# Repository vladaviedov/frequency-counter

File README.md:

# Frequency Counter

Design files & firmware for my [frequency counter
project](https://vladaviedov.org/project/frequency_counter.html)

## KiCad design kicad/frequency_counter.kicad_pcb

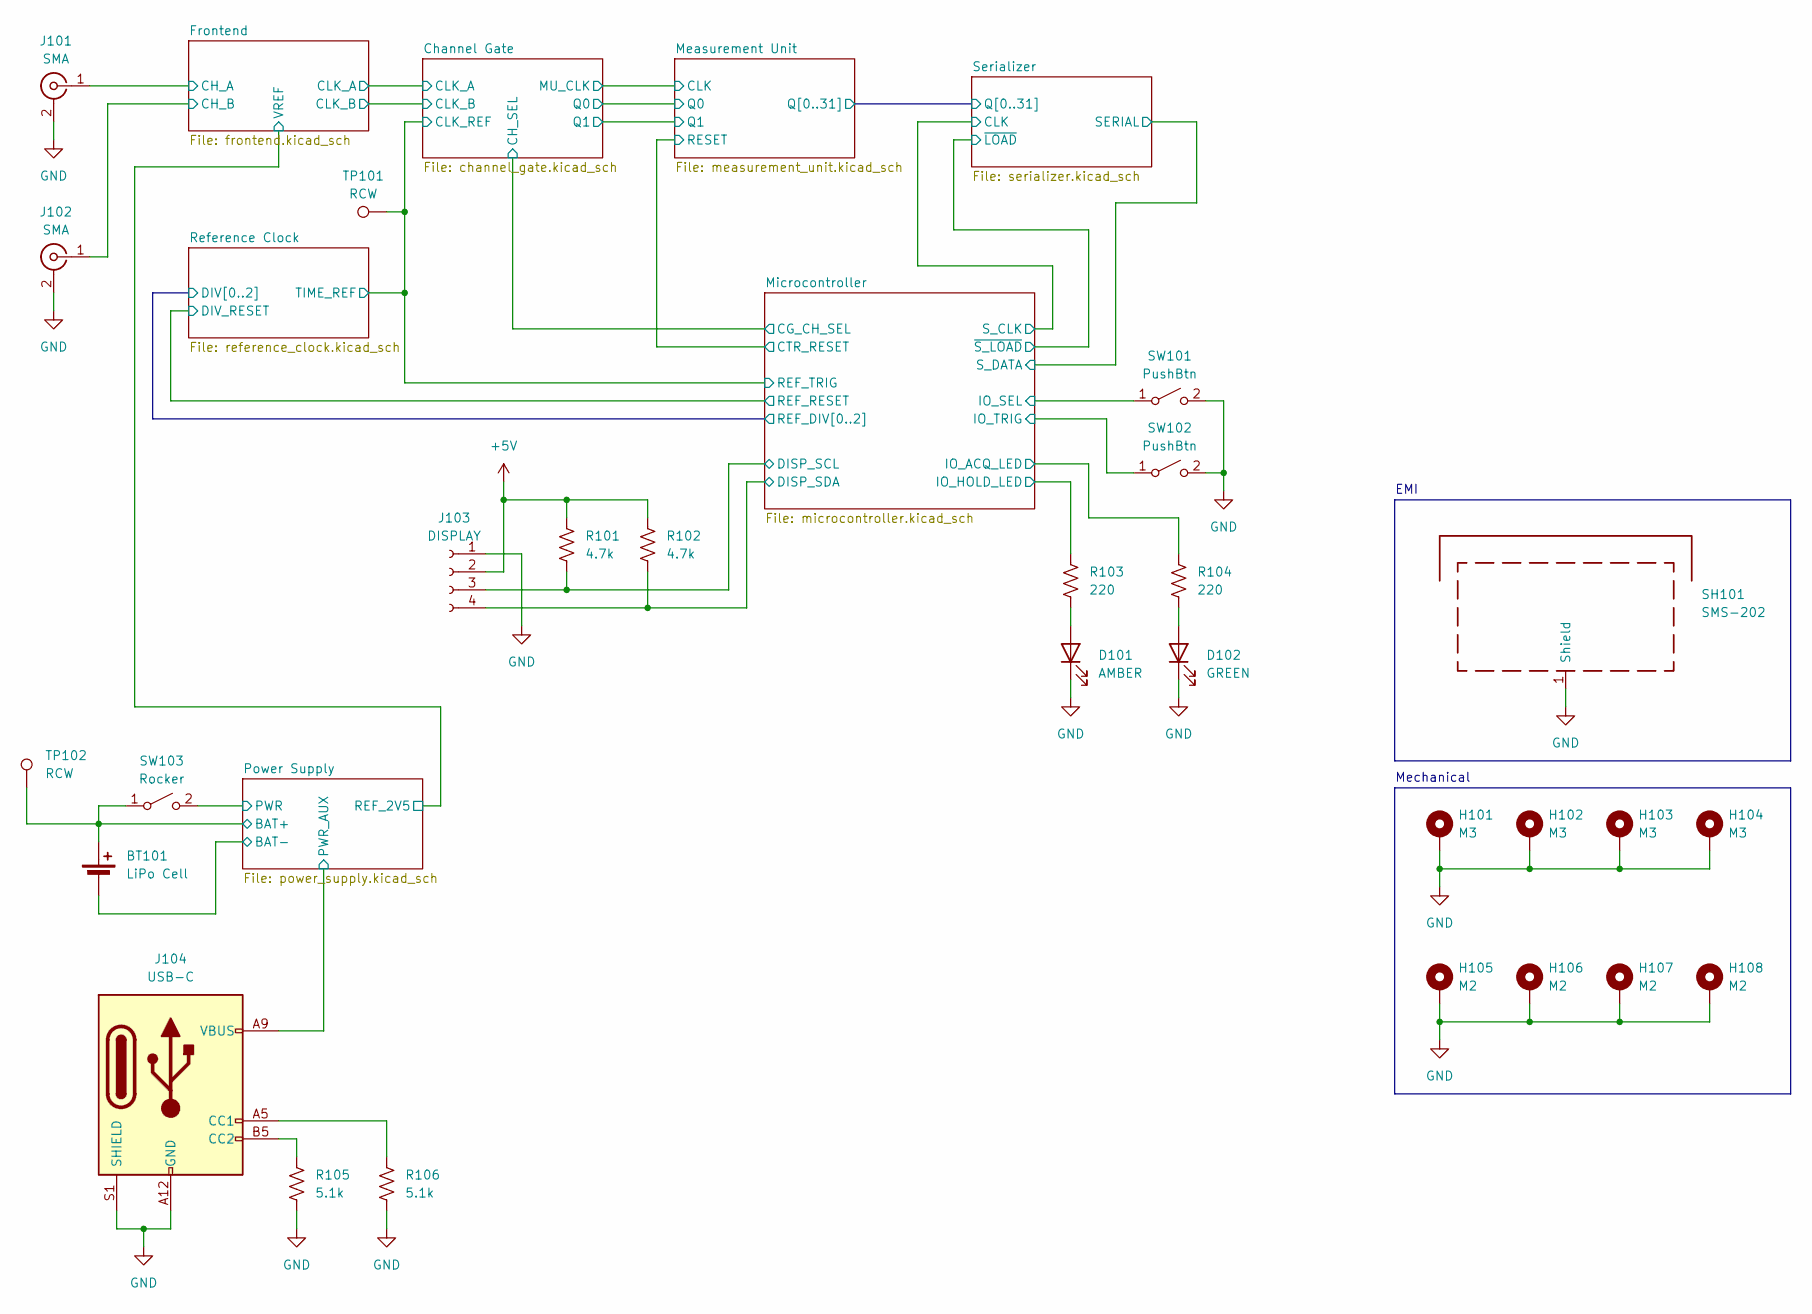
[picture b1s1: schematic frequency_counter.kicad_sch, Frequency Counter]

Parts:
BT101: LiPo Cell; JST_ZH_B2B-ZR_1x02_P1.50mm_Vertical
D101: AMBER; LED_0603_1608Metric; MPN B1911UY--20D000114U1930
D102: GREEN; LED_0603_1608Metric; MPN B1911NG--20D000214U1930
H101, H102, H103, H104: M3; MountingHole_3.2mm_M3_Pad
H105, H106, H107, H108: M2; MountingHole_2.2mm_M2_Pad
J101, J102: SMA; SMA_Adjusted; MPN CON-SMA-EDGE-S
J103: DISPLAY; PinHeader_1x04_P2.54mm_Vertical
J104: USB-C; USB_C_Receptacle_GCT_USB4125-xx-x_6P_TopMnt_Horizontal; MPN USB4125-GF-A
R101, R102: 4.7k; R_0402_1005Metric_Fix; MPN RC0402JR-074K7L
R103, R104: 220; R_0402_1005Metric_Fix; MPN RC0402JR-13220RL
R105, R106: 5.1k; R_0402_1005Metric_Fix; MPN RC0402JR-135K1L
SH101: SMS-202; Laird_Technologies_BMI-S-202-F_16.50x16.50mm; MPN SMS-201F
SW101, SW102: PushBtn; SW_Push_1P1T_NO_E-Switch_TL3301NxxxxxG; MPN 2-1977223-4
SW103: Rocker; SolderWire-1.5sqmm_1x02_P6mm_D1.7mm_OD3mm
TP101, TP102: RCW; TestPoint_KOA_RCW; MPN RCWCTE

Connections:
+5V: J103.2, R101.1, R102.1; also elsewhere on the board
/Channel Gate/CLK_REF: TP101.1; also elsewhere on the board
/Frontend/CH_A: J101.1 (In); also elsewhere on the board
/Frontend/CH_B: J102.1 (In); also elsewhere on the board
/Microcontroller/DISP_SCL: J103.3, R101.2; also elsewhere on the board
/Microcontroller/DISP_SDA: J103.4, R102.2; also elsewhere on the board
/Microcontroller/IO_ACQ_LED: R104.1; also elsewhere on the board
/Microcontroller/IO_HOLD_LED: R103.1; also elsewhere on the board
/Microcontroller/IO_SEL: SW101.1 (A); also elsewhere on the board
/Microcontroller/IO_TRIG: SW102.1 (A); also elsewhere on the board
/Power Supply/BAT+: BT101.1 (+), SW103.1 (A), TP102.1; also elsewhere on the board
/Power Supply/BAT-: BT101.2 (-); also elsewhere on the board
/Power Supply/PWR: SW103.2 (B); also elsewhere on the board
/Power Supply/PWR_AUX: J104.A9 (VBUS), J104.B9 (VBUS); also elsewhere on the board
GND: D101.1 (K), D102.1 (K), H101.1, H102.1, H103.1, H104.1, H105.1, H106.1, H107.1, H108.1, J101.2 (Ext), J102.2 (Ext), J103.1, J104.A12 (GND), J104.B12 (GND), J104.S1 (SHIELD), R105.2, R106.2, SH101.1 (Shield), SW101.2 (B), SW102.2 (B); also elsewhere on the board
unnamed: D101.2 (A), R103.2
unnamed: D102.2 (A), R104.2
unnamed: J104.A5 (CC1), R106.1
unnamed: J104.B5 (CC2), R105.1

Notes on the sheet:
Mechanical
EMI

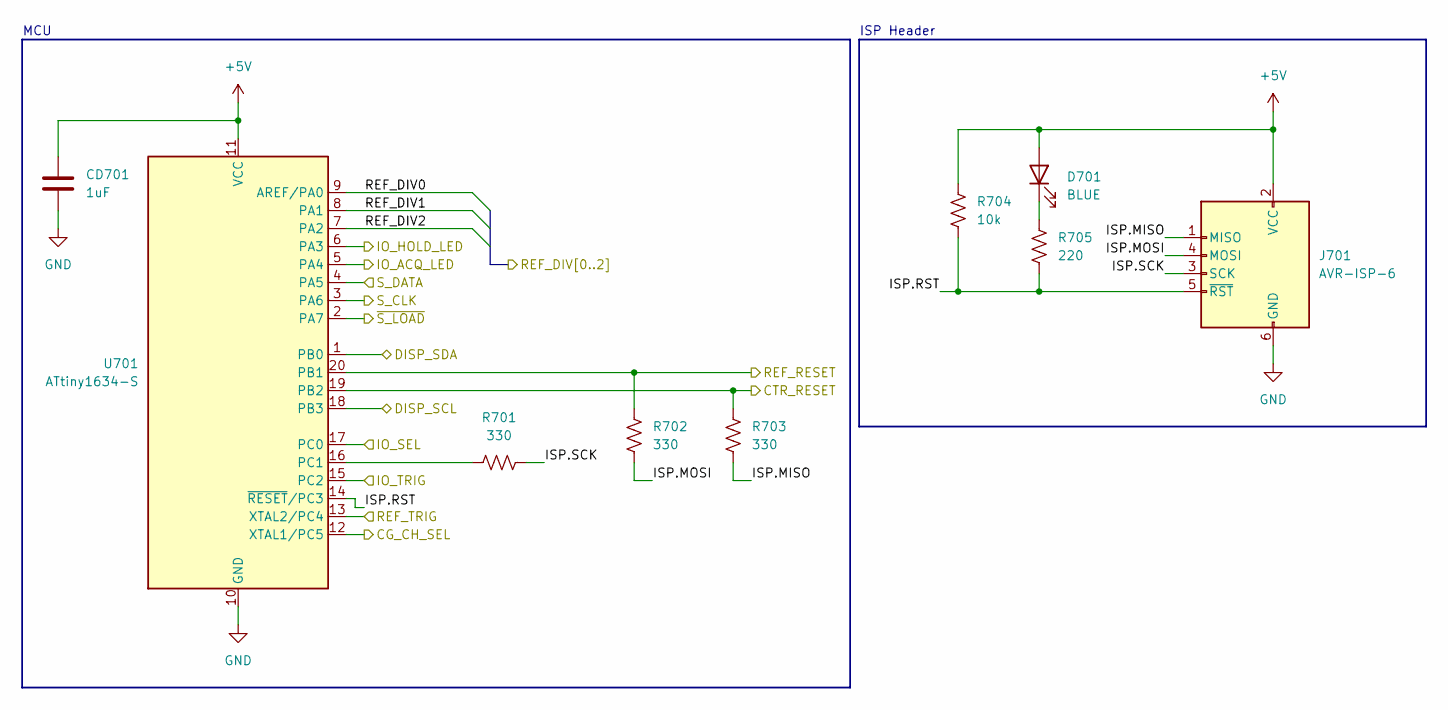
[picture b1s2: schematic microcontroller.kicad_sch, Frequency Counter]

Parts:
CD701: 1uF; C_0402_1005Metric_Fix; MPN 0402ZD105KAT2A
D701: BLUE; LED_0603_1608Metric; MPN E1221NB--05D000814U1930
J701: AVR-ISP-6; IDC-Header_2x03_P2.54mm_Vertical
R701, R702, R703: 330; R_0402_1005Metric_Fix; MPN RC0402JR-13330RL
R704: 10k; R_0402_1005Metric_Fix; MPN RC0402JR-1310KL
R705: 220; R_0402_1005Metric_Fix; MPN RC0402JR-13220RL
U701: ATtiny1634-S; SOIC-20W_7.5x12.8mm_P1.27mm; MPN ATTINY1634-SU

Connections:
+5V: CD701.1, D701.2 (A), J701.2 (VCC), R704.1, U701.11 (VCC); also elsewhere on the board
/Channel Gate/CH_SEL: U701.12 (XTAL1/PC5); also elsewhere on the board
/Channel Gate/CLK_REF: U701.13 (XTAL2/PC4); also elsewhere on the board
/Measurement Unit/RESET: R703.2, U701.19 (PB2); also elsewhere on the board
/Microcontroller/DISP_SCL: U701.18 (PB3); also elsewhere on the board
/Microcontroller/DISP_SDA: U701.1 (PB0); also elsewhere on the board
/Microcontroller/IO_ACQ_LED: U701.5 (PA4); also elsewhere on the board
/Microcontroller/IO_HOLD_LED: U701.6 (PA3); also elsewhere on the board
/Microcontroller/IO_SEL: U701.17 (PC0); also elsewhere on the board
/Microcontroller/IO_TRIG: U701.15 (PC2); also elsewhere on the board
/Microcontroller/ISP.MISO: J701.1 (MISO), R703.1
/Microcontroller/ISP.MOSI: J701.4 (MOSI), R702.2
/Microcontroller/ISP.RST: J701.5 (~RST), R704.2, R705.1, U701.14 (~RESET/PC3)
/Microcontroller/ISP.SCK: J701.3 (SCK), R701.1
/Microcontroller/REF_DIV0: U701.9 (AREF/PA0); also elsewhere on the board
/Microcontroller/REF_DIV1: U701.8 (PA1); also elsewhere on the board
/Microcontroller/REF_DIV2: U701.7 (PA2); also elsewhere on the board
/Microcontroller/REF_RESET: R702.1, U701.20 (PB1); also elsewhere on the board
/Microcontroller/S_CLK: U701.3 (PA6); also elsewhere on the board
/Microcontroller/S_DATA: U701.4 (PA5); also elsewhere on the board
/Microcontroller/~S_LOAD: U701.2 (PA7); also elsewhere on the board
GND: CD701.2, J701.6 (GND), U701.10 (GND); also elsewhere on the board
unnamed: D701.1 (K), R705.2
unnamed: R701.2, U701.16 (PC1)

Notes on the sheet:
MCU
ISP Header

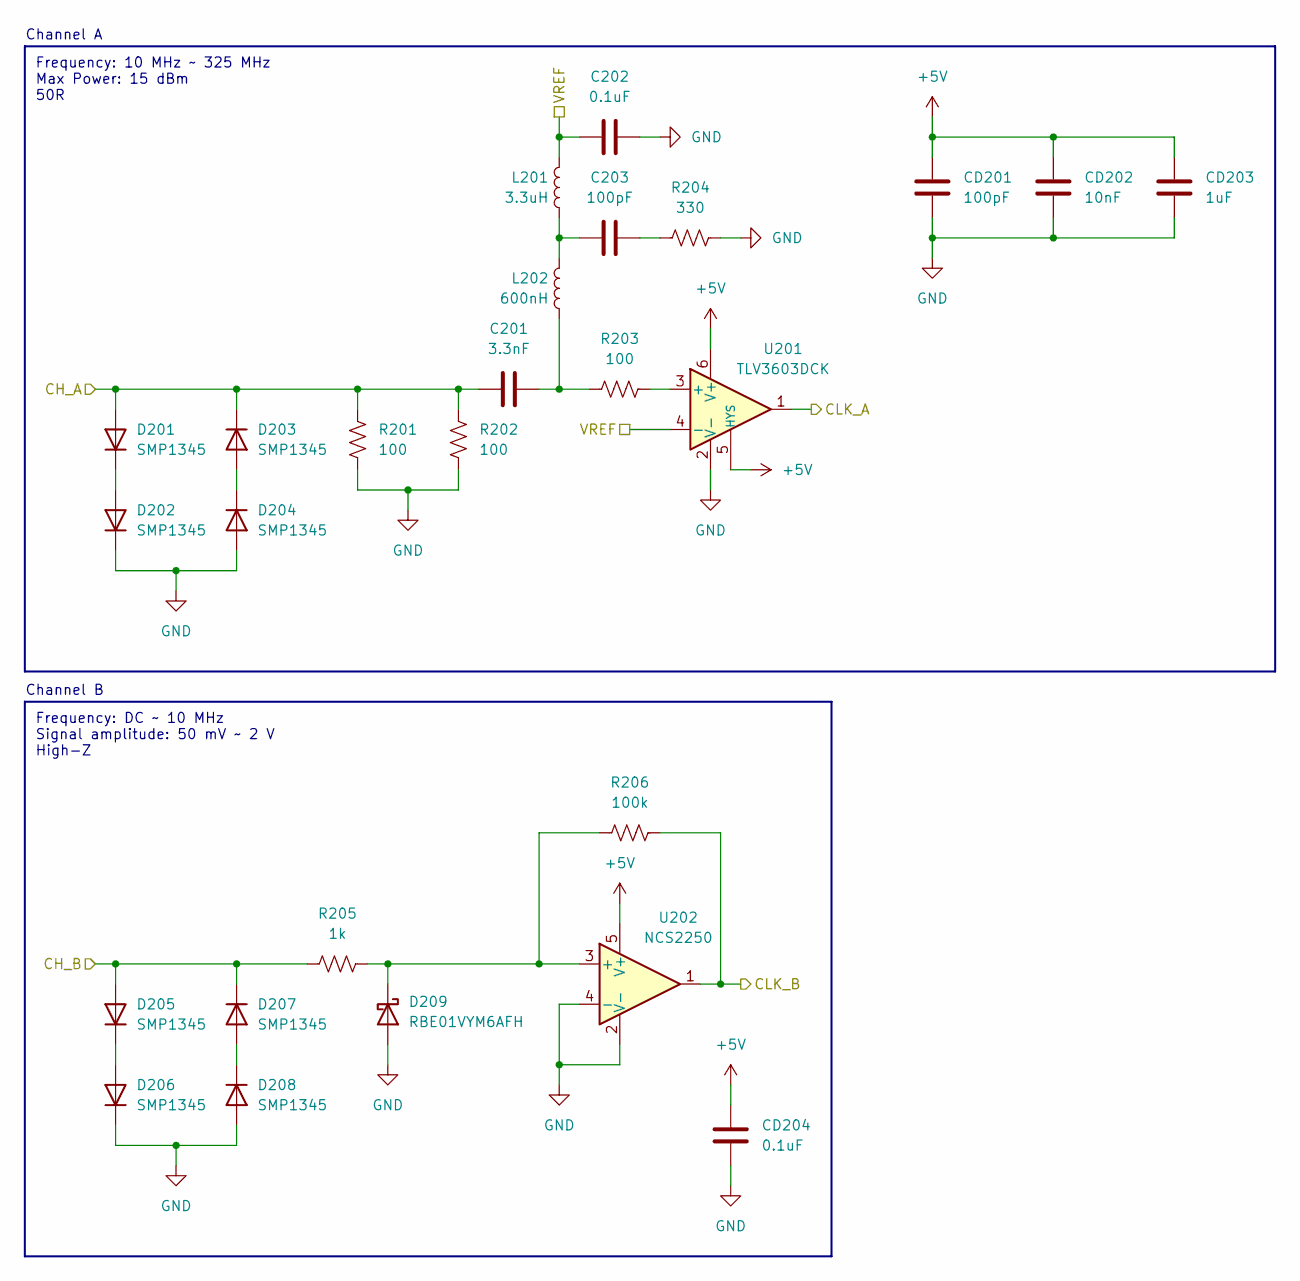
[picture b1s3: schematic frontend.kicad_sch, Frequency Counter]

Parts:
C201: 3.3nF; C_0402_1005Metric_Fix; MPN GRM1555C1H332JE01D
C202: 0.1uF; C_0402_1005Metric_Fix; MPN KGM05AR51C104KH
C203: 100pF; C_0402_1005Metric_Fix; MPN CC0402JRNPO9BN101
CD201: 100pF; C_0402_1005Metric_Fix; MPN CC0402JRNPO9BN101
CD202: 10nF; C_0402_1005Metric_Fix; MPN GRM155R71C103KA01D
CD203: 1uF; C_0402_1005Metric_Fix; MPN 0402ZD105KAT2A
CD204: 0.1uF; C_0402_1005Metric_Fix; MPN KGM05AR51C104KH
D201, D202, D203, D204, D205, D206, D207, D208: SMP1345; D_0402_1005Metric_Pad0.77x0.64mm_HandSolder; MPN SMP1345-040LF
D209: RBE01VYM6AFH; D_SOD-323_HandSoldering; MPN RBE01VYM6AFHTR
L201: 3.3uH; L_0805_2012Metric; MPN BRC2012T3R3MD
L202: 600nH; L_0603_1608Metric; MPN 7447610260
R201, R202: 100; R_1206_3216Metric; MPN RT1206BRE07100RL
R203: 100; R_0402_1005Metric_Fix; MPN RC0402JR-07100RL
R204: 330; R_0402_1005Metric_Fix; MPN RC0402JR-13330RL
R205: 1k; R_0402_1005Metric_Fix; MPN RC0402JR-071KL
R206: 100k; R_0402_1005Metric_Fix; MPN RC0402JR-07100RL
U201: TLV3603DCK; SOT-363_SC-70-6; MPN TLV3603DCKR
U202: NCS2250; TSOP-5_1.65x3.05mm_P0.95mm; MPN NCS2250SN2T1G

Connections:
+5V: CD201.1, CD202.1, CD203.1, CD204.1, U201.5 (HYS), U201.6 (V+), U202.5 (V+); also elsewhere on the board
/Channel Gate/CLK_A: U201.1; also elsewhere on the board
/Channel Gate/CLK_B: R206.2, U202.1; also elsewhere on the board
/Frontend/CH_A: C201.1, D201.2 (A), D203.1 (K), R201.2, R202.2; also elsewhere on the board
/Frontend/CH_B: D205.2 (A), D207.1 (K), R205.1; also elsewhere on the board
/Frontend/VREF: C202.1, L201.1, U201.4 (-); also elsewhere on the board
GND: C202.2, CD201.2, CD202.2, CD203.2, CD204.2, D202.1 (K), D204.2 (A), D206.1 (K), D208.2 (A), D209.2 (A), R201.1, R202.1, R204.2, U201.2 (V-), U202.2 (V-), U202.4 (-); also elsewhere on the board
unnamed: C201.2, L202.2, R203.1
unnamed: C203.1, L201.2, L202.1
unnamed: C203.2, R204.1
unnamed: D201.1 (K), D202.2 (A)
unnamed: D203.2 (A), D204.1 (K)
unnamed: D205.1 (K), D206.2 (A)
unnamed: D207.2 (A), D208.1 (K)
unnamed: D209.1 (K), R205.2, R206.1, U202.3 (+)
unnamed: R203.2, U201.3 (+)

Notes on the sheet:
Frequency: 10 MHz ~ 325 MHz Max Power: 15 dBm 50R
Channel B
Channel A
Frequency: DC ~ 10 MHz Signal amplitude: 50 mV ~ 2 V High-Z

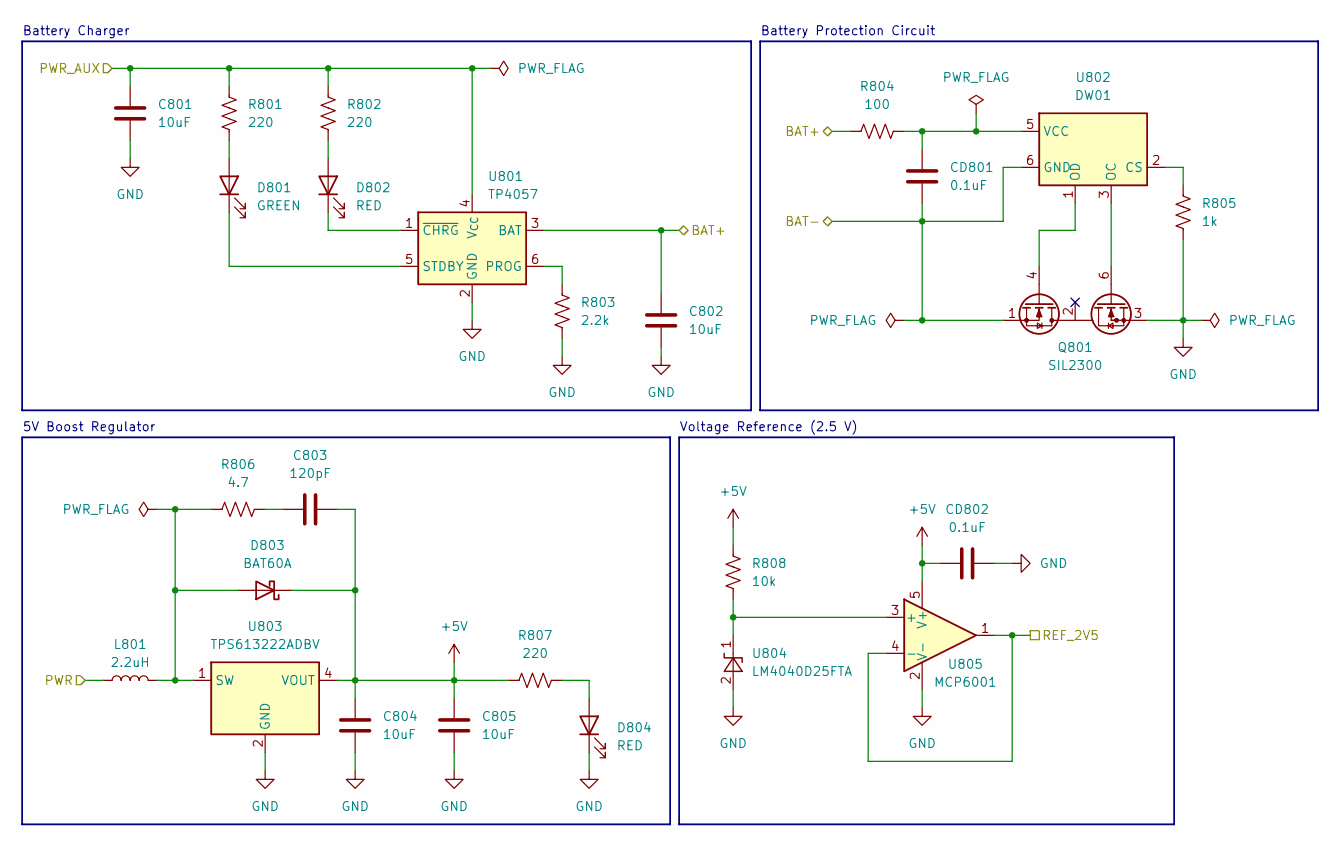
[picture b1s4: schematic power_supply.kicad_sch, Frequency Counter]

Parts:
C801, C802, C804, C805: 10uF; C_0603_1608Metric; MPN CL10A106KP8NNNC
C803: 120pF; C_0402_1005Metric_Fix; MPN GRM1555C1H121JA01D
CD801, CD802: 0.1uF; C_0402_1005Metric_Fix; MPN KGM05AR51C104KH
D801: GREEN; LED_0603_1608Metric; MPN B1911NG--20D000214U1930
D802, D804: RED; LED_0603_1608Metric; MPN B1911USD-20D000114U1930
D803: BAT60A; D_SOD-323; MPN BAT60A
L801: 2.2uH; L_1008_2520Metric; MPN DFE252012F-2R2M=P2
Q801: SIL2300; SOT-23-6; MPN SIL2300-TP
R801, R802, R807: 220; R_0402_1005Metric_Fix; MPN RC0402JR-13220RL
R803: 2.2k; R_0402_1005Metric_Fix; MPN RC0402JR-132K2L
R804: 100; R_0402_1005Metric_Fix; MPN RC0402JR-07100RL
R805: 1k; R_0402_1005Metric_Fix; MPN RC0402JR-071KL
R806: 4.7; R_0805_2012Metric; MPN RC0805FR-134R7L
R808: 10k; R_0402_1005Metric_Fix; MPN RC0402JR-1310KL
U801: TP4057; TSOT-23-6; MPN TP4057TP4057
U802: DW01; SOT-23-6; MPN DW01
U803: TPS613222ADBV; SOT-23-5; MPN TPS613222ADBVR
U804: LM4040D25FTA; SOT-23-3; MPN LM4040D25FTA
U805: MCP6001; SOT-353_SC-70-5; MPN MCP6001T-I/OT

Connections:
+5V: C803.2, C804.1, C805.1, CD802.1, D803.1 (K), R807.1, R808.1, U803.4 (VOUT), U805.5 (V+); also elsewhere on the board
/Frontend/VREF: U805.1, U805.4 (-); also elsewhere on the board
/Power Supply/BAT+: C802.1, R804.1, U801.3 (BAT); also elsewhere on the board
/Power Supply/BAT-: CD801.2, Q801.1 (S1), U802.6 (GND); also elsewhere on the board
/Power Supply/PWR: L801.1; also elsewhere on the board
/Power Supply/PWR_AUX: C801.1, R801.1, R802.1, U801.4 (V_{CC}); also elsewhere on the board
GND: C801.2, C802.2, C804.2, C805.2, CD802.2, D804.1 (K), Q801.3 (S2), R803.2, R805.1, U801.2 (GND), U803.2 (GND), U804.2 (A), U805.2 (V-); also elsewhere on the board
unnamed: C803.1, R806.2
unnamed: D801.2 (A), R801.2
unnamed: D801.1 (K), U801.5 (STDBY)
unnamed: D802.2 (A), R802.2
unnamed: D802.1 (K), U801.1 (~CHRG)
unnamed: D803.2 (A), L801.2, R806.1, U803.1 (SW)
unnamed: D804.2 (A), R807.2
unnamed: Q801.4 (G1), U802.1 (OD)
unnamed: Q801.6 (G2), U802.3 (OC)
unnamed: R803.1, U801.6 (PROG)
unnamed: R805.2, U802.2 (CS)
unnamed: CD801.1, R804.2, U802.5 (VCC)
unnamed: R808.2, U804.1 (K), U805.3 (+)

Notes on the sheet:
5V Boost Regulator
Battery Protection Circuit
Voltage Reference (2.5 V)
Battery Charger

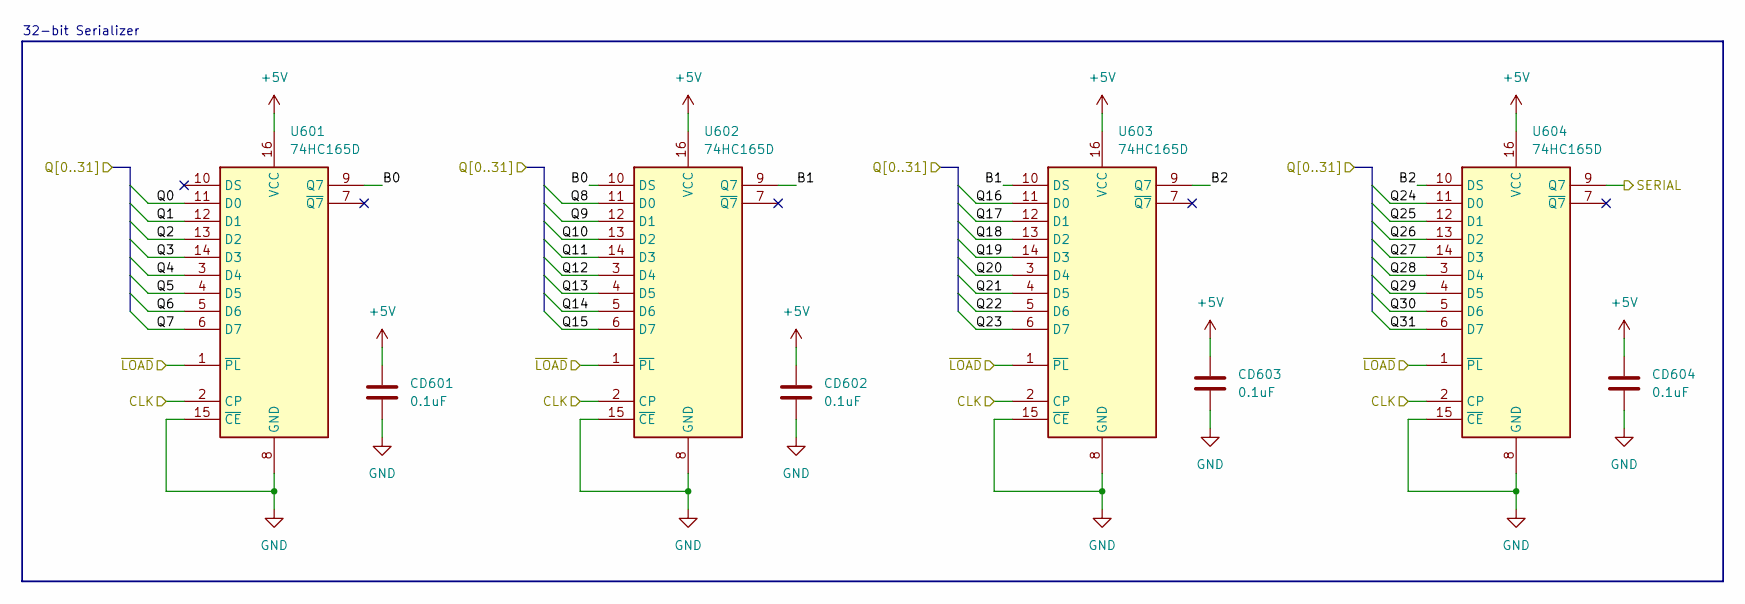
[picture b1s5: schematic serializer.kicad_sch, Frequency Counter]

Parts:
CD601, CD602, CD603, CD604: 0.1uF; C_0402_1005Metric_Fix; MPN KGM05AR51C104KH
U601, U602, U603, U604: 74HC165D; SO-16_3.9x9.9mm_P1.27mm; MPN 74HC165D,653

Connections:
+5V: CD601.1, CD602.1, CD603.1, CD604.1, U601.16 (VCC), U602.16 (VCC), U603.16 (VCC), U604.16 (VCC); also elsewhere on the board
/Measurement Unit/Q0: U601.11 (D0); also elsewhere on the board
/Measurement Unit/Q1: U601.12 (D1); also elsewhere on the board
/Measurement Unit/Q2: U601.13 (D2); also elsewhere on the board
/Measurement Unit/Q3: U601.14 (D3); also elsewhere on the board
/Measurement Unit/Q4: U601.3 (D4); also elsewhere on the board
/Measurement Unit/Q5: U601.4 (D5); also elsewhere on the board
/Measurement Unit/Q6: U601.5 (D6); also elsewhere on the board
/Measurement Unit/Q7: U601.6 (D7); also elsewhere on the board
/Measurement Unit/Q8: U602.11 (D0); also elsewhere on the board
/Measurement Unit/Q9: U602.12 (D1); also elsewhere on the board
/Measurement Unit/Q10: U602.13 (D2); also elsewhere on the board
/Measurement Unit/Q11: U602.14 (D3); also elsewhere on the board
/Measurement Unit/Q12: U602.3 (D4); also elsewhere on the board
/Measurement Unit/Q13: U602.4 (D5); also elsewhere on the board
/Measurement Unit/Q14: U602.5 (D6); also elsewhere on the board
/Measurement Unit/Q15: U602.6 (D7); also elsewhere on the board
/Measurement Unit/Q16: U603.11 (D0); also elsewhere on the board
/Measurement Unit/Q17: U603.12 (D1); also elsewhere on the board
/Measurement Unit/Q18: U603.13 (D2); also elsewhere on the board
/Measurement Unit/Q19: U603.14 (D3); also elsewhere on the board
/Measurement Unit/Q20: U603.3 (D4); also elsewhere on the board
/Measurement Unit/Q21: U603.4 (D5); also elsewhere on the board
/Measurement Unit/Q22: U603.5 (D6); also elsewhere on the board
/Measurement Unit/Q23: U603.6 (D7); also elsewhere on the board
/Measurement Unit/Q24: U604.11 (D0); also elsewhere on the board
/Measurement Unit/Q25: U604.12 (D1); also elsewhere on the board
/Measurement Unit/Q26: U604.13 (D2); also elsewhere on the board
/Measurement Unit/Q27: U604.14 (D3); also elsewhere on the board
/Measurement Unit/Q28: U604.3 (D4); also elsewhere on the board
/Measurement Unit/Q29: U604.4 (D5); also elsewhere on the board
/Measurement Unit/Q30: U604.5 (D6); also elsewhere on the board
/Measurement Unit/Q31: U604.6 (D7); also elsewhere on the board
/Microcontroller/S_CLK: U601.2 (CP), U602.2 (CP), U603.2 (CP), U604.2 (CP); also elsewhere on the board
/Microcontroller/S_DATA: U604.9 (Q7); also elsewhere on the board
/Microcontroller/~S_LOAD: U601.1 (~PL), U602.1 (~PL), U603.1 (~PL), U604.1 (~PL); also elsewhere on the board
/Serializer/B0: U601.9 (Q7), U602.10 (DS)
/Serializer/B1: U602.9 (Q7), U603.10 (DS)
/Serializer/B2: U603.9 (Q7), U604.10 (DS)
GND: CD601.2, CD602.2, CD603.2, CD604.2, U601.8 (GND), U601.15 (~CE), U602.8 (GND), U602.15 (~CE), U603.8 (GND), U603.15 (~CE), U604.8 (GND), U604.15 (~CE); also elsewhere on the board

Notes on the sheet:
32-bit Serializer

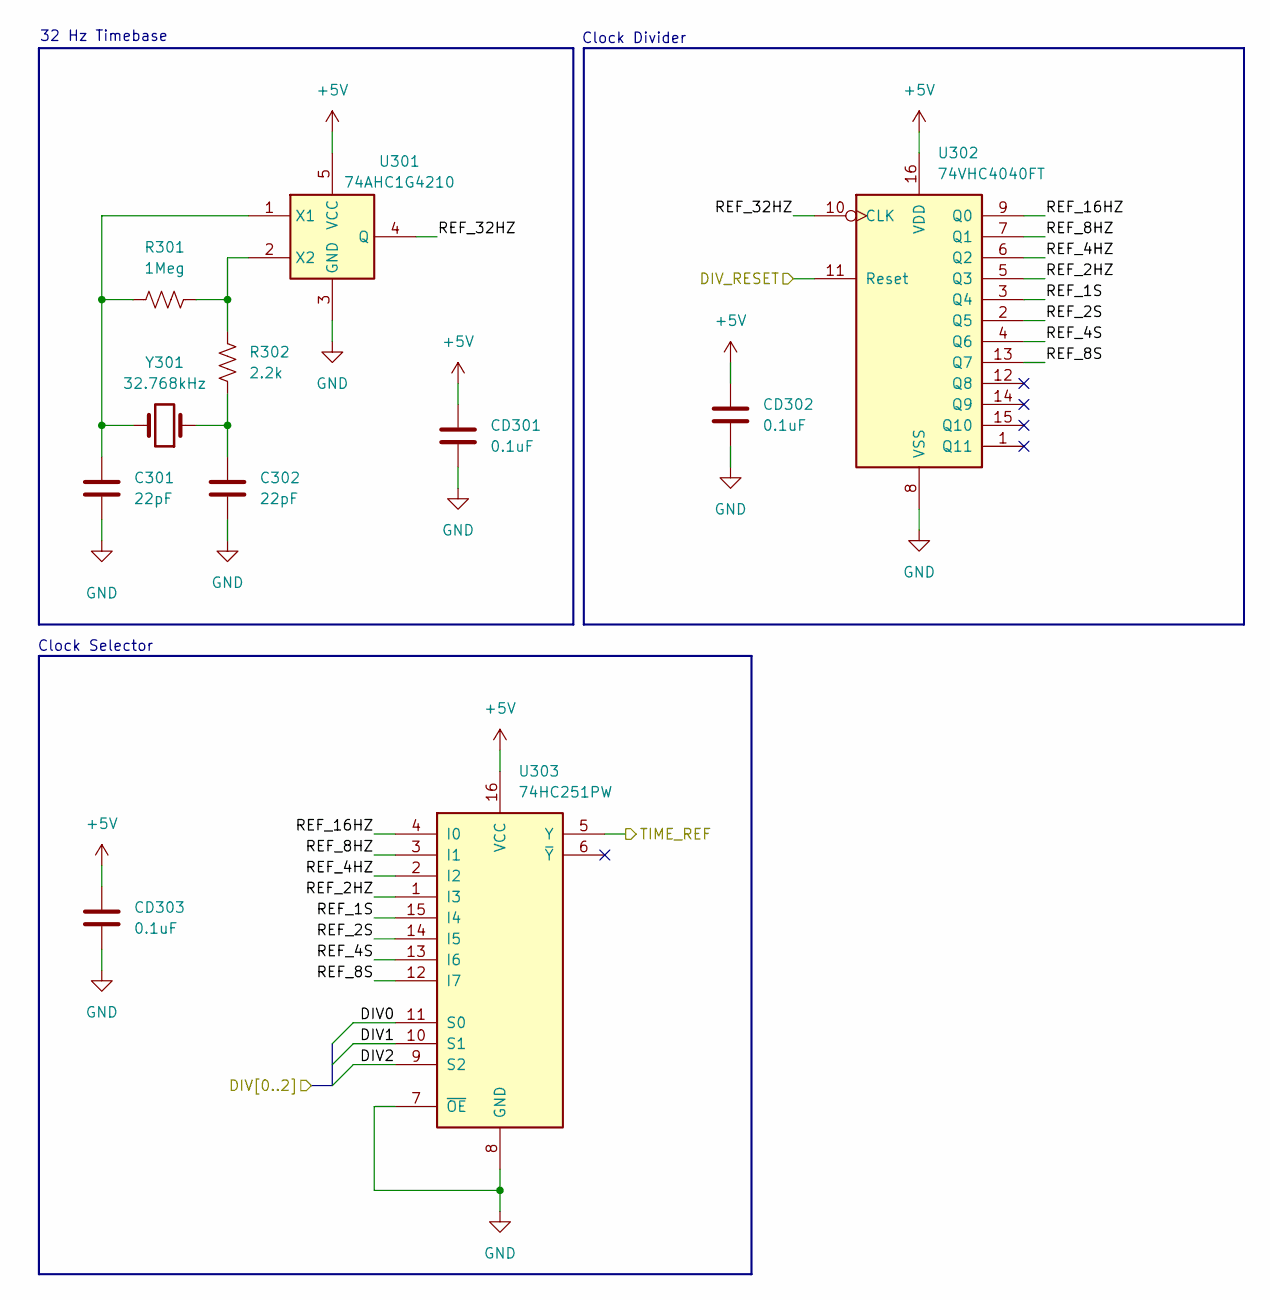
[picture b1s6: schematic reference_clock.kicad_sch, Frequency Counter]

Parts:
C301, C302: 22pF; C_0402_1005Metric_Fix; MPN GRM1555C1H220JA01D
CD301, CD302, CD303: 0.1uF; C_0402_1005Metric_Fix; MPN KGM05AR51C104KH
R301: 1Meg; R_0402_1005Metric_Fix; MPN RC0402FR-071ML
R302: 2.2k; R_0402_1005Metric_Fix; MPN RC0402JR-132K2L
U301: 74AHC1G4210; SOT-353_SC-70-5; MPN 74AHC1G4210GWH
U302: 74VHC4040FT; TSSOP-16_4.4x5mm_P0.65mm; MPN 74VHC4040FT
U303: 74HC251PW; TSSOP-16_4.4x5mm_P0.65mm; MPN 74HC251PW,118
Y301: 32.768kHz; Crystal_SMD_EuroQuartz_EQ161-2Pin_3.2x1.5mm_HandSoldering; MPN CM315D32768HZFT

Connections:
+5V: CD301.1, CD302.1, CD303.1, U301.5 (VCC), U302.16 (VDD), U303.16 (VCC); also elsewhere on the board
/Channel Gate/CLK_REF: U303.5 (Y); also elsewhere on the board
/Microcontroller/REF_DIV0: U303.11 (S0); also elsewhere on the board
/Microcontroller/REF_DIV1: U303.10 (S1); also elsewhere on the board
/Microcontroller/REF_DIV2: U303.9 (S2); also elsewhere on the board
/Microcontroller/REF_RESET: U302.11 (Reset); also elsewhere on the board
/Reference Clock/REF_1S: U302.3 (Q4), U303.15 (I4)
/Reference Clock/REF_2HZ: U302.5 (Q3), U303.1 (I3)
/Reference Clock/REF_2S: U302.2 (Q5), U303.14 (I5)
/Reference Clock/REF_4HZ: U302.6 (Q2), U303.2 (I2)
/Reference Clock/REF_4S: U302.4 (Q6), U303.13 (I6)
/Reference Clock/REF_8HZ: U302.7 (Q1), U303.3 (I1)
/Reference Clock/REF_8S: U302.13 (Q7), U303.12 (I7)
/Reference Clock/REF_16HZ: U302.9 (Q0), U303.4 (I0)
/Reference Clock/REF_32HZ: U301.4 (Q), U302.10 (CLK)
GND: C301.2, C302.2, CD301.2, CD302.2, CD303.2, U301.3 (GND), U302.8 (VSS), U303.7 (~OE), U303.8 (GND); also elsewhere on the board
unnamed: C302.1, R302.2, Y301.1
unnamed: C301.1, R301.1, U301.1 (X1), Y301.2
unnamed: R301.2, R302.1, U301.2 (X2)

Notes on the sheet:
Clock Divider
32 Hz Timebase
Clock Selector

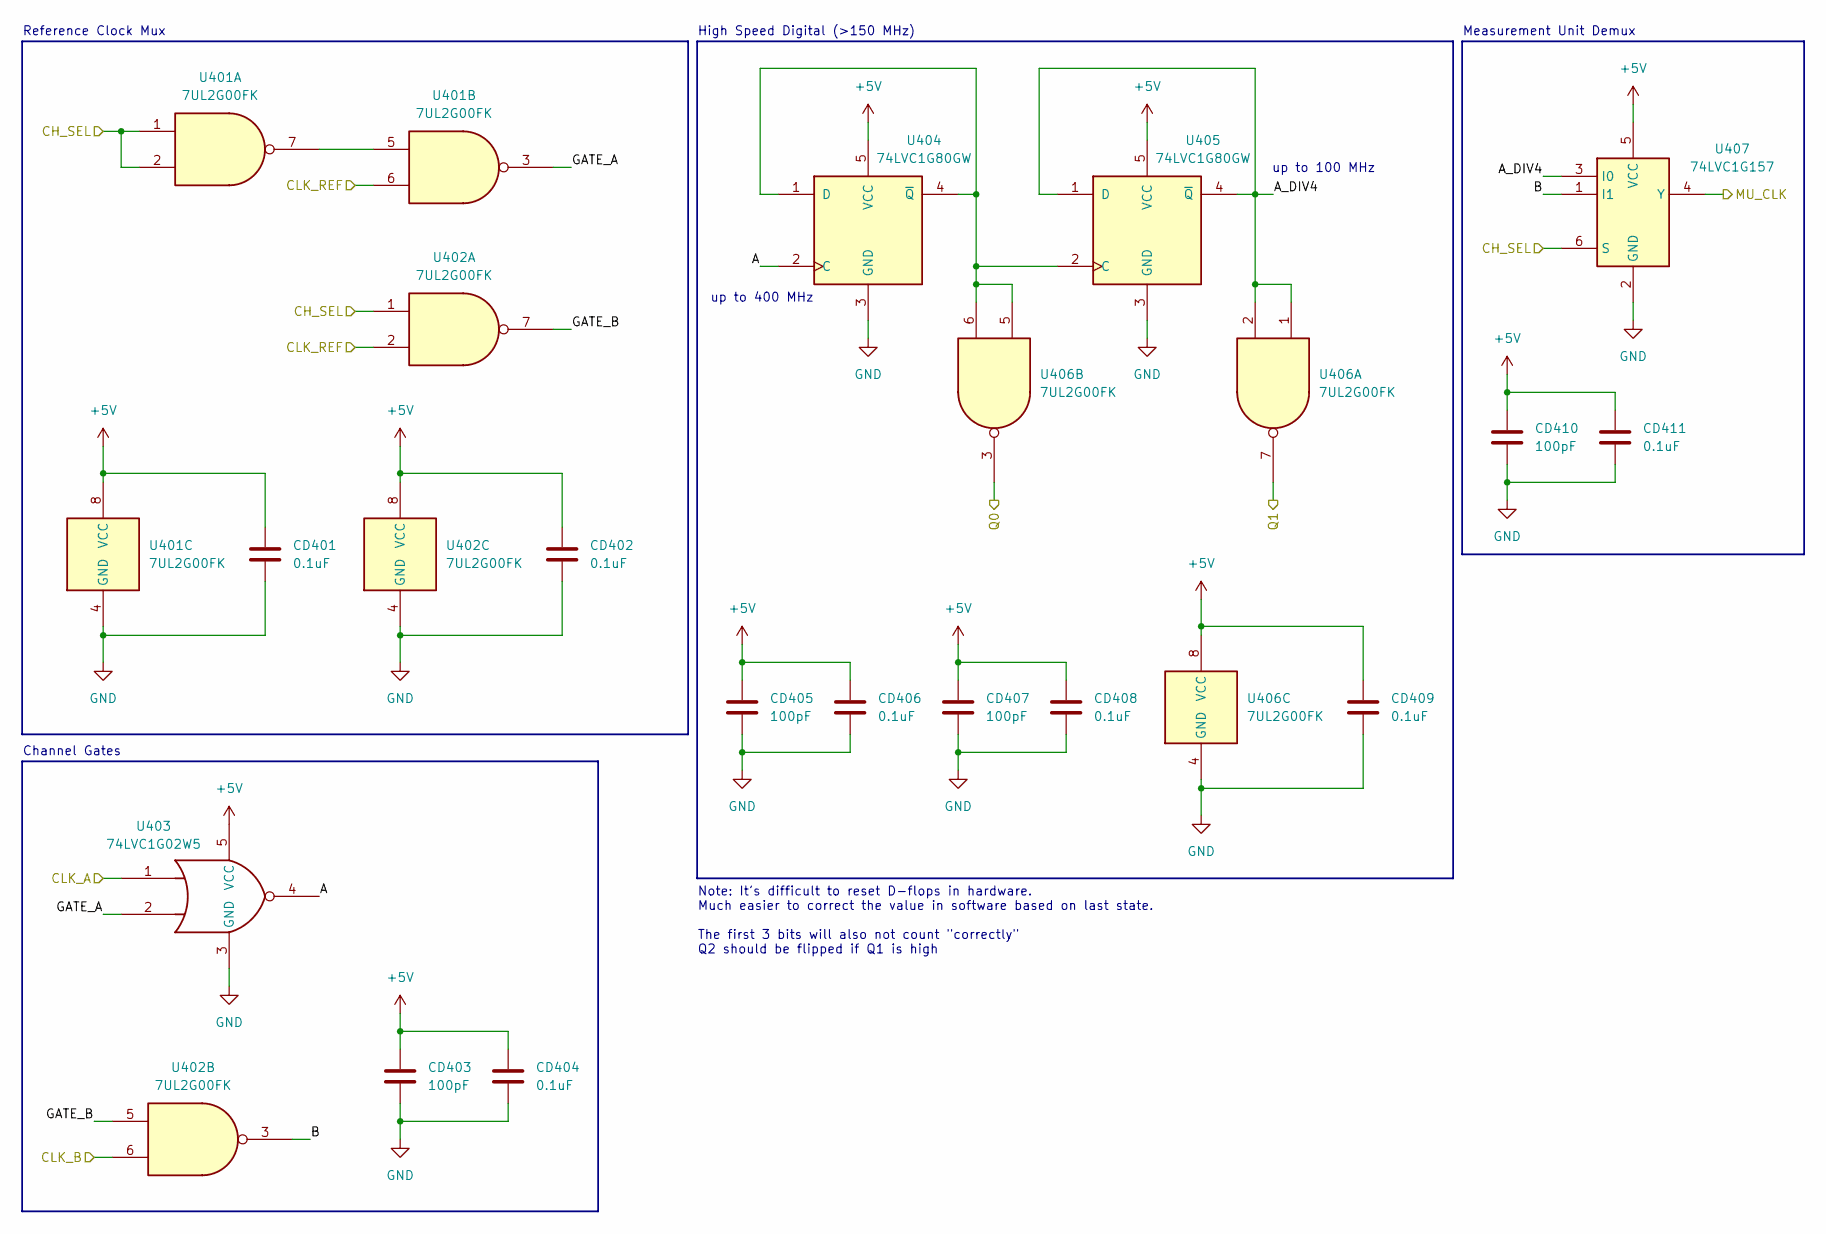
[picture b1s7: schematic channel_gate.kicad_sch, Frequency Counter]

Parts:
CD401, CD402, CD404, CD406, CD408, CD409, CD411: 0.1uF; C_0402_1005Metric_Fix; MPN KGM05AR51C104KH
CD403, CD405, CD407, CD410: 100pF; C_0402_1005Metric_Fix; MPN CC0402JRNPO9BN101
U401, U402, U406: 7UL2G00FK; VSSOP-8_2.3x2mm_P0.5mm; MPN 7UL2G00FK,LF
U403: 74LVC1G02W5; SC-74A-5_1.55x2.9mm_P0.95mm; MPN 74LVC1G02W5-7
U404, U405: 74LVC1G80GW; SOT-353_SC-70-5; MPN 74LVC1G80GW,125
U407: 74LVC1G157; TSOP-6_1.65x3.05mm_P0.95mm; MPN 74LVC1G157GW,125

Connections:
+5V: CD401.1, CD402.1, CD403.1, CD404.1, CD405.1, CD406.1, CD407.1, CD408.1, CD409.1, CD410.1, CD411.1, U401.8 (VCC), U402.8 (VCC), U403.5 (VCC), U404.5 (VCC), U405.5 (VCC), U406.8 (VCC), U407.5 (VCC); also elsewhere on the board
/Channel Gate/A: U403.4, U404.2 (C)
/Channel Gate/A_DIV4: U405.1 (D), U405.4 (~Q), U406.1, U406.2, U407.3 (I0)
/Channel Gate/B: U402.3, U407.1 (I1)
/Channel Gate/CH_SEL: U401.1, U401.2, U402.1, U407.6 (S); also elsewhere on the board
/Channel Gate/CLK_A: U403.1; also elsewhere on the board
/Channel Gate/CLK_B: U402.6; also elsewhere on the board
/Channel Gate/CLK_REF: U401.6, U402.2; also elsewhere on the board
/Channel Gate/GATE_A: U401.3, U403.2
/Channel Gate/GATE_B: U402.5, U402.7
/Channel Gate/MU_CLK: U407.4 (Y); also elsewhere on the board
/Measurement Unit/Q0: U406.3; also elsewhere on the board
/Measurement Unit/Q1: U406.7; also elsewhere on the board
GND: CD401.2, CD402.2, CD403.2, CD404.2, CD405.2, CD406.2, CD407.2, CD408.2, CD409.2, CD410.2, CD411.2, U401.4 (GND), U402.4 (GND), U403.3 (GND), U404.3 (GND), U405.3 (GND), U406.4 (GND), U407.2 (GND); also elsewhere on the board
unnamed: U401.5, U401.7
unnamed: U404.1 (D), U404.4 (~Q), U405.2 (C), U406.5, U406.6

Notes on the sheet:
High Speed Digital (>150 MHz)
Channel Gates
up to 400 MHz
Note: It's difficult to reset D-flops in hardware. Much easier to correct the value in software based on last state. The first 3 bits will also not count "correctly" Q2 should be flipped if Q1 is high
up to 100 MHz
Measurement Unit Demux
Reference Clock Mux
